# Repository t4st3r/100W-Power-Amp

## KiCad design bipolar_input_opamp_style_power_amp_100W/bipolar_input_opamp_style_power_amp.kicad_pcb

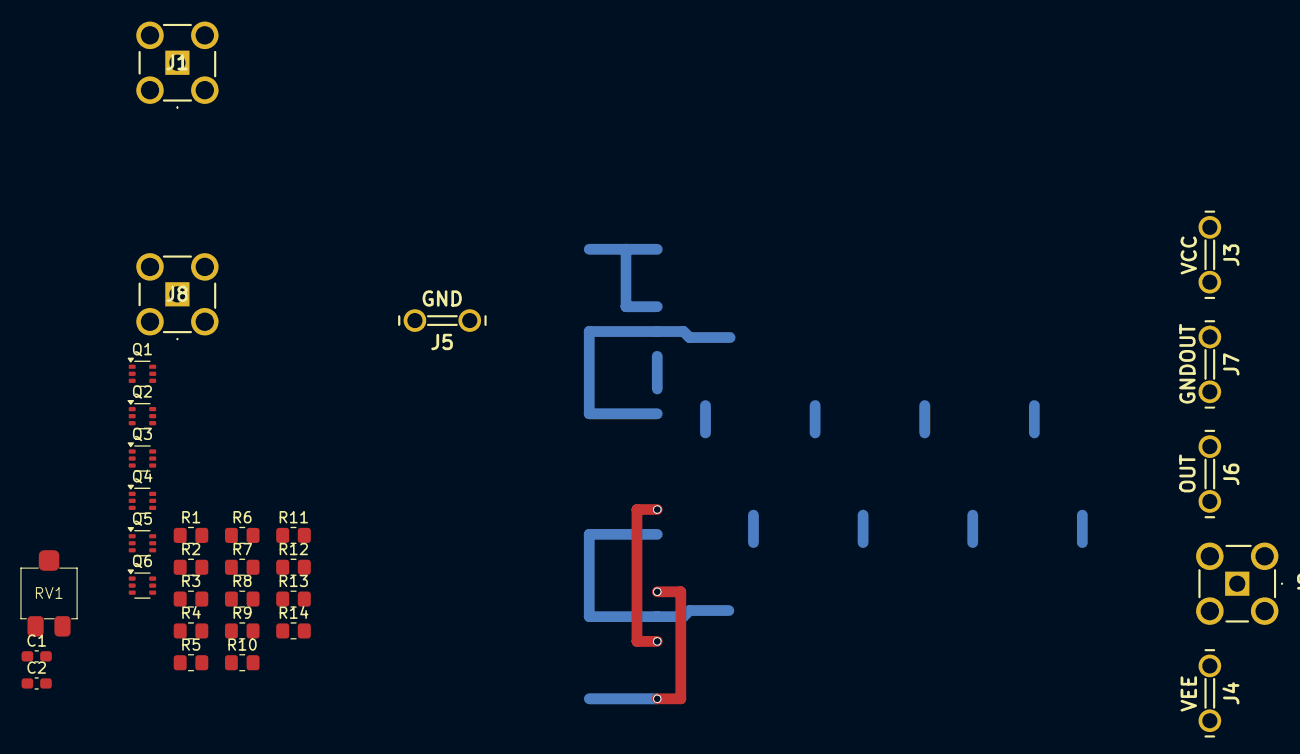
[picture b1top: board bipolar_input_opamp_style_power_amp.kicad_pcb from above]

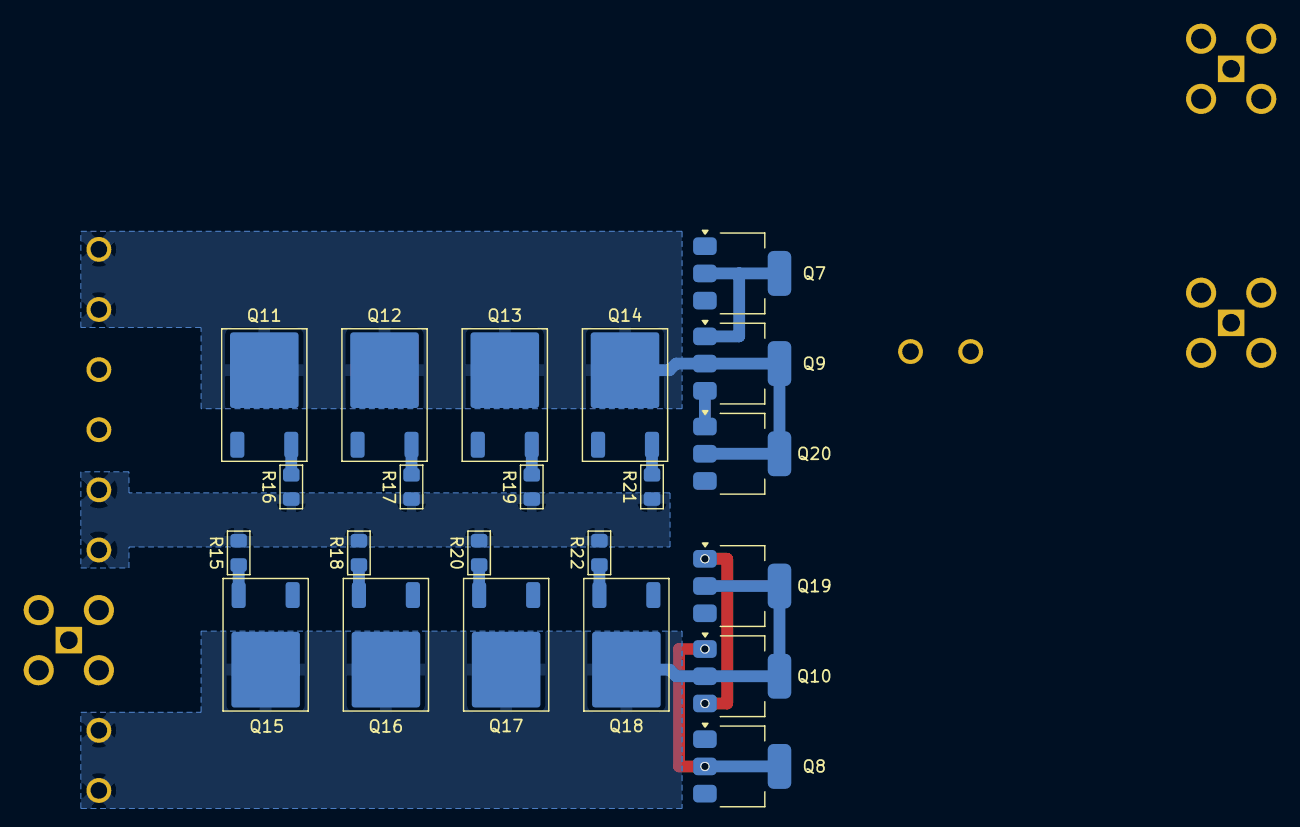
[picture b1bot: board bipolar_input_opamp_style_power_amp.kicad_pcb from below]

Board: 2 copper layers, 53 parts (22 on the bottom side), 39 nets.

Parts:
C1, C2: 47p; C_0603_1608Metric_Pad1.08x0.95mm_HandSolder
J1: -IN; SMA6251A13GT50G50
J2: MON; SMA6251A13GT50G50
J3: VCC; 726386-2
J4: VEE; 726386-2
J5: GND; 726386-2
J6: OUT; 726386-2
J7: GNDOUT; 726386-2
J8: +IN; SMA6251A13GT50G50
Q1, Q4, Q5: MMDT5401; SOT-363_SC-70-6
Q2, Q3, Q6: MMDT5551; SOT-363_SC-70-6
Q7, Q10, Q19: PZTA92-QX; SOT-223
Q8, Q9, Q20: PZTA42-QX; SOT-223
Q11, Q12, Q13, Q14: MJD31C; TO-252-2
Q15, Q16, Q17, Q18: MJD32C; TO-252-2
R1, R3, R4, R5, R6, R7, R8, R9, R14: 1k; R_0805_2012Metric_Pad1.20x1.40mm_HandSolder
R2: 330k; R_0805_2012Metric_Pad1.20x1.40mm_HandSolder
R10, R11: 47R; R_0805_2012Metric_Pad1.20x1.40mm_HandSolder
R12: 100R; R_0805_2012Metric_Pad1.20x1.40mm_HandSolder
R13: GAIN; R_0805_2012Metric_Pad1.20x1.40mm_HandSolder
R15, R16, R17, R18, R19, R20, R21, R22: 50m; R_0805_2012Metric_Pad1.15x1.40mm_HandSolder
RV1: 500R; G43B_SMD_trimpot

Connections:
GND: J1.2, J1.3, J1.4, J1.5, J2.2, J2.3, J2.4, J2.5, J5.1, J5.2, J7.1, J7.2, J8.2, J8.3, J8.4, J8.5, R14.2
IN+: J8.1, Q3.2 (B1), Q4.2 (B1)
IN-: J1.1, Q3.5 (B2), Q4.5 (B2), R13.2, R14.1
unnamed: Q1.2 (B1), Q1.3 (C2), Q1.5 (B2), R2.2
unnamed: Q1.6 (C1), Q4.1 (E1), Q4.4 (E2)
unnamed: Q1.1 (E1), R4.1
unnamed: Q1.4 (E2), R1.1
unnamed: Q2.2 (B1), Q2.3 (C2), Q2.5 (B2), R2.1
unnamed: Q2.6 (C1), Q3.1 (E1), Q3.4 (E2)
unnamed: Q2.1 (E1), R5.2
unnamed: Q2.4 (E2), R3.2
unnamed: C1.2, Q3.6 (C1), Q5.2 (B1), Q5.3 (C2), Q5.5 (B2), Q7.1 (B)
unnamed: Q3.3 (C2), Q5.6 (C1)
unnamed: C2.1, Q4.6 (C1), Q6.2 (B1), Q6.3 (C2), Q6.5 (B2), Q8.1 (B)
unnamed: Q4.3 (C2), Q6.6 (C1)
unnamed: Q5.1 (E1), R8.1
unnamed: Q5.4 (E2), R6.1
unnamed: Q6.1 (E1), R9.2
unnamed: Q6.4 (E2), R7.2
unnamed: Q7.3 (E), R10.1
unnamed: Q8.3 (E), R11.2
unnamed: Q7.2 (C), Q7.4 (C), Q9.1 (B), R12.2
unnamed: Q8.2 (C), Q8.4 (C), Q10.1 (B), RV1.3
unnamed: Q10.3 (E), Q19.1 (B)
unnamed: Q11.1 (B), Q12.1 (B), Q13.1 (B), Q14.1 (B), Q20.3 (E)
unnamed: Q11.3 (E), R16.2
unnamed: Q12.3 (E), R17.2
unnamed: Q13.3 (E), R19.2
unnamed: Q14.3 (E), R21.2
unnamed: Q15.1 (B), Q16.1 (B), Q17.1 (B), Q18.1 (B), Q19.3 (E)
unnamed: Q15.3 (E), R15.1
unnamed: Q16.3 (E), R18.1
unnamed: Q17.3 (E), R20.1
unnamed: Q18.3 (E), R22.1
unnamed: Q9.3 (E), Q20.1 (B)
unnamed: R12.1, RV1.1, RV1.2
OUT: C1.1, C2.2, J2.1, J6.1, J6.2, R13.1, R15.2, R16.1, R17.1, R18.2, R19.1, R20.2, R21.1, R22.2
VCC: J3.1, J3.2, Q9.2 (C), Q9.4 (C), Q11.2 (C), Q12.2 (C), Q13.2 (C), Q14.2 (C), Q20.2 (C), Q20.4 (C), R1.2, R4.2, R6.2, R8.2, R10.2
VEE: J4.1, J4.2, Q10.2 (C), Q10.4 (C), Q15.2 (C), Q16.2 (C), Q17.2 (C), Q18.2 (C), Q19.2 (C), Q19.4 (C), R3.1, R5.1, R7.1, R9.1, R11.1

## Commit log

2025-02-09 Initial commit - first prototype for this power
